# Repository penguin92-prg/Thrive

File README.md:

# Thrive 2026 Main-repo

このリポジトリは RCJ サッカー オープンリーグ に出場する、チーム Thrive のリポジトリです。

### Follow us!
様々な情報を公開していこうと考えています！ぜひのぞいてみてください！
- X (Twitter) | [@RCJ_thrive](https://x.com/RCJ_thrive)
- YouTube | [@RCJ_thrive](https://youtube.com/@rcj_thrive)
- Team Web Page | [Thrive Blog](https://note.com/rcj_thrive)

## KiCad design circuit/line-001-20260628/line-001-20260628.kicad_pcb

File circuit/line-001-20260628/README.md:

# ラインセンサ基板 001

ラインセンサ基板 ver.001のREADME

## 設計者
- @penguin92-prg
- @ryo-robot14

## ピンアサイン

## 使用上の注意

## 使用部品

|No.|Ref.|Name|QTY|Assembled By|Note|URL|
|---|---|---|---|---|---|---|
|001|D1~40|OSR5JA3Z74A|40|OWN|赤色LED|[秋月電子](https://akizukidenshi.com/catalog/g/g111577/)|
|002|R41~72,77~80|Resister 10kΩ|34|JLCPCB|LED用75Ω|[JLCPCB](https://jlcpcb.com/partdetail/21350-0805W8F750JT5E_SMTonly/C20638)|
|003|Q1~40|NJL7502L|40|OWN|フォトトランジスタ|[秋月電子](https://akizukidenshi.com/catalog/g/g102325/)|
|004|R1~32,38,40|Resister 10kΩ|34|JLCPCB|プルダウン用100kΩ|[JLCPCB](https://jlcpcb.com/partdetail/18102-0805W8F1002T5E/C17414)|
|005|U1~16,19,20|LM339DR|20|JLCPCB|コンパレータ|[JLCPCB](https://jlcpcb.com/partdetail/TexasInstruments-LM393DR/C67470)|
|006|C1~16,23,24|Capacitor 100nF|20|JLCPCB|コンパレータ用バイパスコンデンサ|[JLCPCB](https://jlcpcb.com/partdetail/YAGEO-CC0805KRX7R9BB104/C49678)|
|007|C21,22,26,27|Capacitor 10uF|4|JLCPCB|PWM平滑化用コンデンサ|[JLCPCB](https://jlcpcb.com/partdetail/439567-GRM21BR61H106KE43L/C440198)|
|008|R83,84,87,88|Resister 1kΩ|4|JLCPCB|PWM平滑化用抵抗器|[JLCPCB](https://jlcpcb.com/partdetail/18201-0805W8F1001T5E/C17513)|
|009|U17|ATMega2560-16A|1|OWN||[秋月電子](https://akizukidenshi.com/catalog/g/g116567/)|
|010|C28|Capacitor 100nF|1|JLCPCB|ATMegaARFF用コンデンサ|[JLCPCB](https://jlcpcb.com/partdetail/YAGEO-CC0805KRX7R9BB104/C49678)|
|011|SW1|TVBP06-B043C|1|OWN|ATMegaRST用白色タクトスイッチ|[秋月電子](https://akizukidenshi.com/catalog/g/g108074/)|
|012|C18|Capacitor 100nF|1|JLCPCB|ATMegaRST用コンデンサ|[JLCPCB](https://jlcpcb.com/partdetail/YAGEO-CC0805KRX7R9BB104/C49678)|
|013|R81|Resister 10kΩ|1|JLCPCB|ATMegaRST用抵抗器|[JLCPCB](https://jlcpcb.com/partdetail/18102-0805W8F1002T5E/C17414)|
|014|C20|Capacitor 100uF|1|JLCPCB|ATMega用バルクコンデンサ|[JLCPCB](https://jlcpcb.com/partdetail/15681-CL31A107MQHNNNE/C15008)|
|015|C34~38|Capacitor 100nF|5|JLCPCB|ATMega用バイパスコンデンサ|[JLCPCB](https://jlcpcb.com/partdetail/YAGEO-CC0805KRX7R9BB104/C49678)|
|016|SW2|SS12D01G4|1|OWN|5V切り替え用スライドスイッチ|[秋月電子](https://akizukidenshi.com/catalog/g/g112723/)|
|017|J3|コネクタハウジング 02x03|1|OWN|ICSP用ハウジング（配線を介すること）|[秋月電子](https://akizukidenshi.com/catalog/g/g112435/)|
|018|D41|OSG50603C1E|1|OWN|信号緑色LED|[秋月電子](https://akizukidenshi.com/catalog/g/g108275/)|
|019|D42|OSWT1608C1A|1|OWN|信号青色LED|[秋月電子](https://akizukidenshi.com/catalog/g/g103986/)|
|020|R85,86|Resister 330Ω|2|JLCPCB|LED用抵抗器|[JLCPCB](https://jlcpcb.com/partdetail/18318-0805W8F3300T5E/C17630)|
|021|U18|CH340G|1|OWN|USB-UART変換IC|[秋月電子](https://akizukidenshi.com/catalog/g/g113544/)|
|022|C31,32,33|Capacitor 100nF|3|JLCPCB|CH340G用コンデンサ|[JLCPCB](https://jlcpcb.com/partdetail/YAGEO-CC0805KRX7R9BB104/C49678)|
|023|R93|Resister 4.7kΩ|1|JLCPCB|CH340G用抵抗器|[JLCPCB](https://jlcpcb.com/partdetail/18361-0805W8F4701T5E/C17673)|
|024|Y1|Crystal 16MHz|1|OWN|クリスタル|[秋月電子](https://akizukidenshi.com/catalog/g/g108671/)|
|025|C17,19|Capacitor 22pF|2|JLCPCB|クリスタル用コンデンサ|[JLCPCB](https://jlcpcb.com/partdetail/2005-CL10C220JB8NNNC/C1653)|
|026|R82|Resister 1MΩ||JLCPCB|クリスタル用抵抗器|[JLCPCB](https://jlcpcb.com/partdetail/18202-0805W8F1004T5E/C17514)|
|027|Y2|Crystal 12MHz|1|OWN|クリスタル|[秋月電子](https://akizukidenshi.com/catalog/g/g108669/)|
|028|C29,30|Capacitor 22pF|2|JLCPCB|クリスタル用コンデンサ|[JLCPCB](https://jlcpcb.com/partdetail/2005-CL10C220JB8NNNC/C1653)|
|029|R89|Resister 1MΩ|1|JLCPCB|クリスタル用抵抗器|[JLCPCB](https://jlcpcb.com/partdetail/18202-0805W8F1004T5E/C17514)|
|030|P1|USB Type-C|1|OWN|1|[秋月電子](https://akizukidenshi.com/catalog/g/g114356/)|
|031|R90,91|Resister 5.1kΩ|2|JLCPCB|USB用抵抗器|[JLCPCB](https://jlcpcb.com/partdetail/28584-0805W8F5101T5E/C27834)|
|032|D43|CH213K|1|OWN|USB用理想ダイオード|[秋月電子](https://akizukidenshi.com/catalog/g/g129462/)|
|033|D44|OSR50603C1E|1|OWN|VBUS確認用LED|[秋月電子](https://akizukidenshi.com/catalog/g/g108274/)|
|034|R92|Resister 330Ω|1|JLCPCB|VBUS確認用抵抗器|[JLCPCB](https://jlcpcb.com/partdetail/18318-0805W8F3300T5E/C17630)|
|035|J1|XT30U-M|1|OWN|供給基板との接続|[秋月電子](https://akizukidenshi.com/catalog/g/g117951/)|
|036|J2|---|-|---|2pin配線を直接実装すること|---|

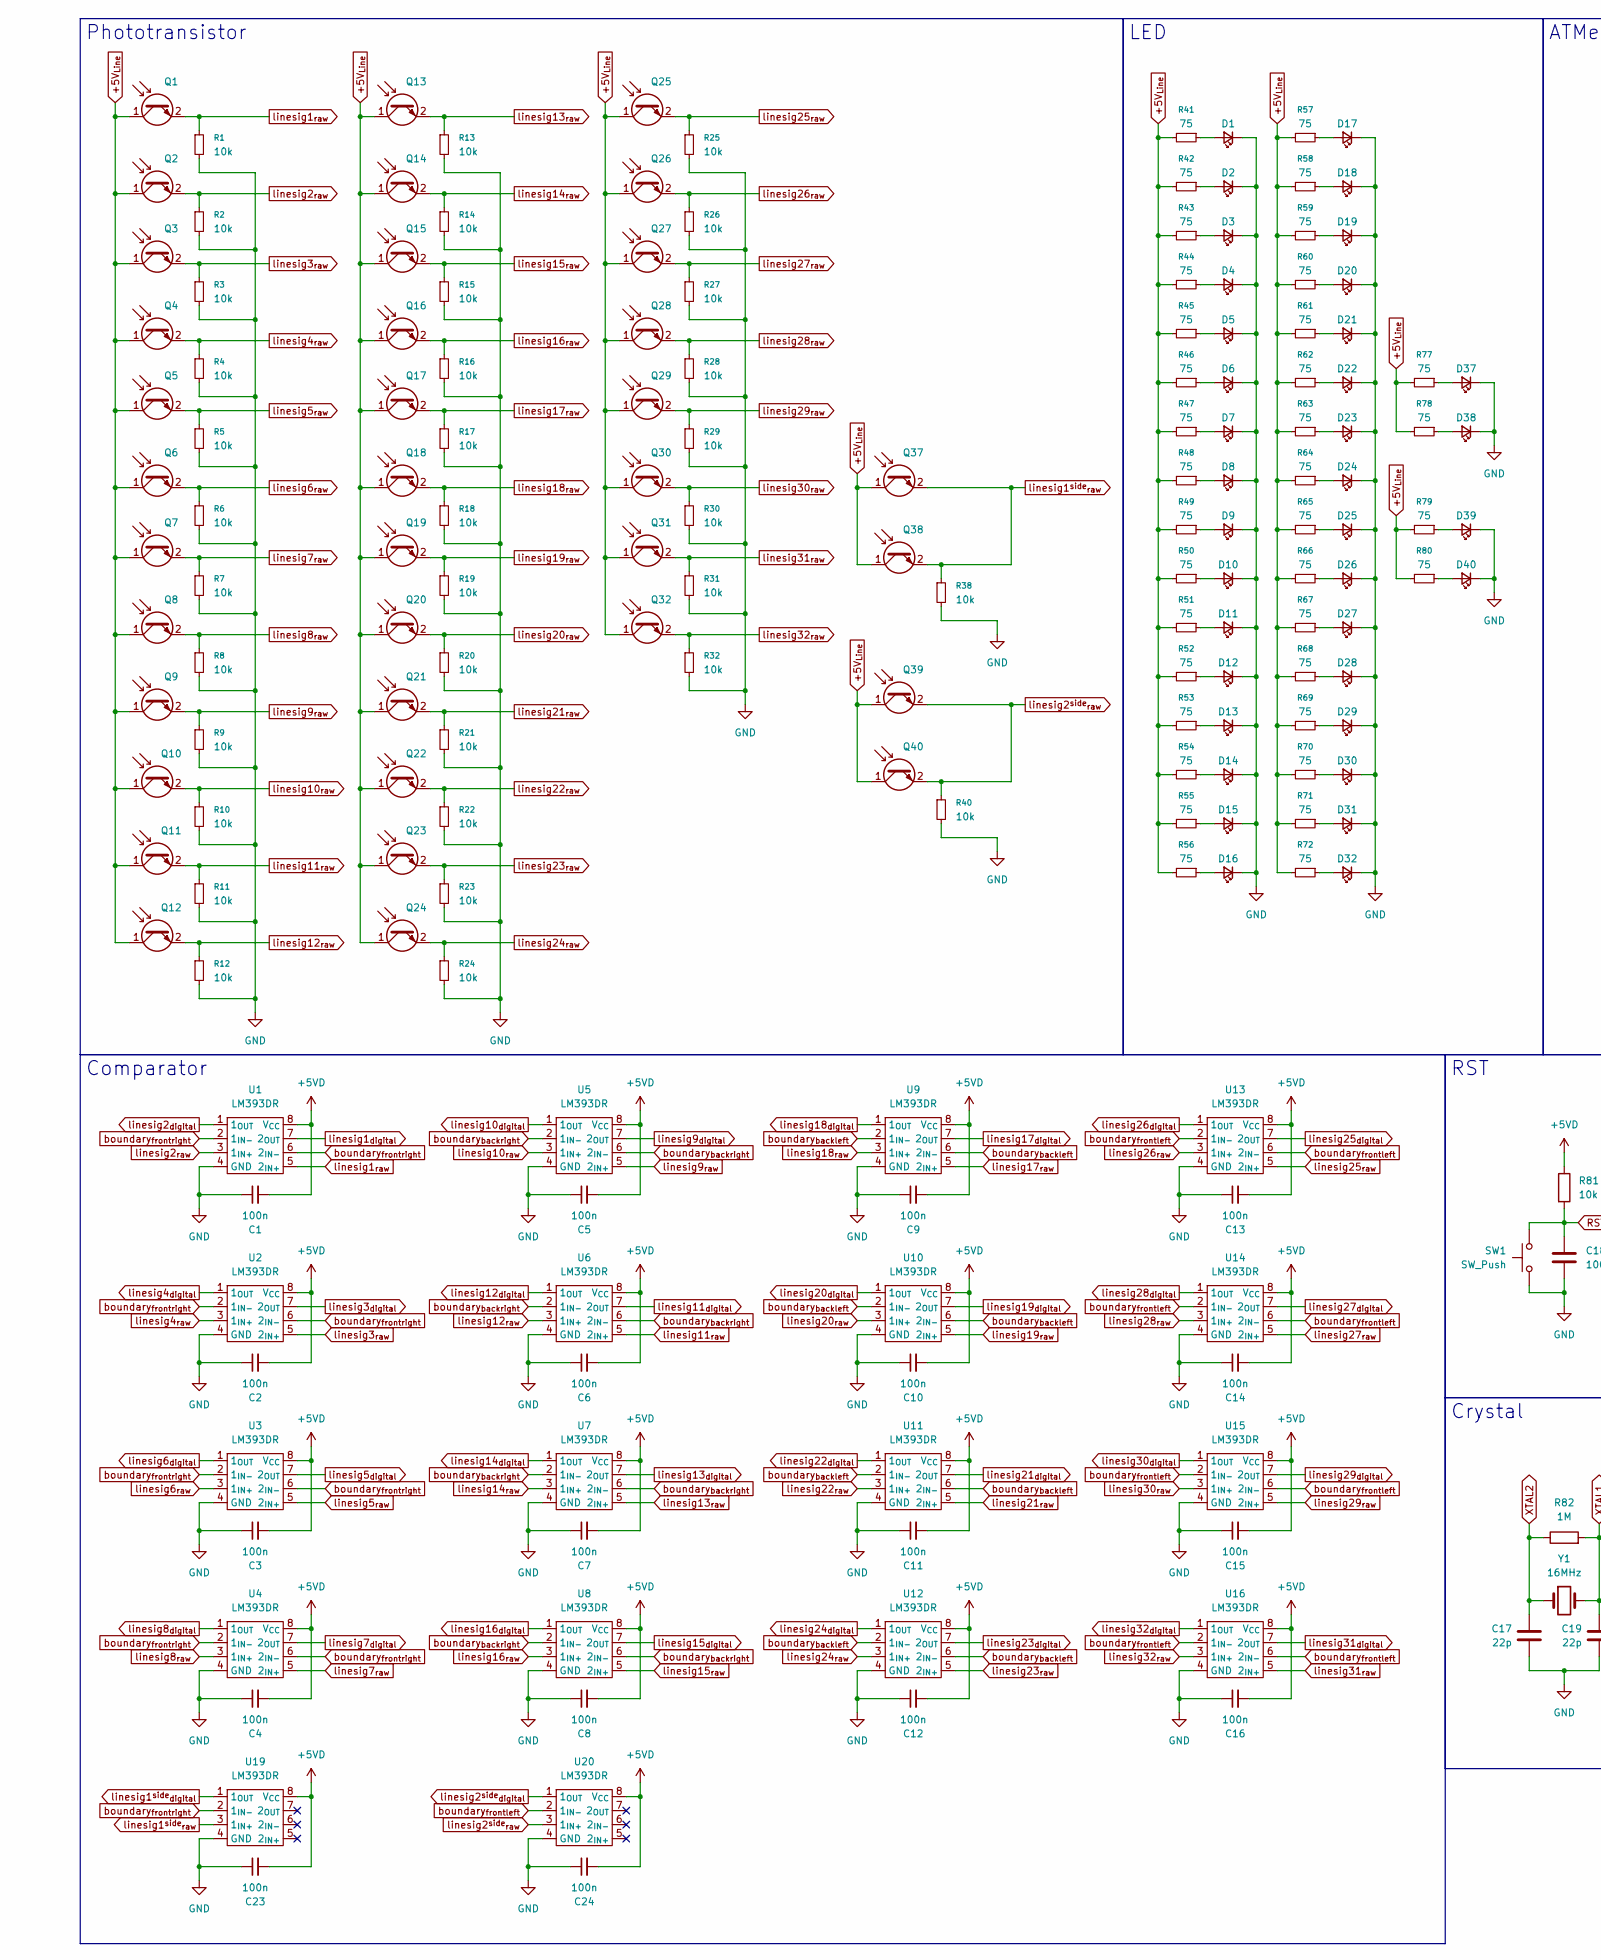
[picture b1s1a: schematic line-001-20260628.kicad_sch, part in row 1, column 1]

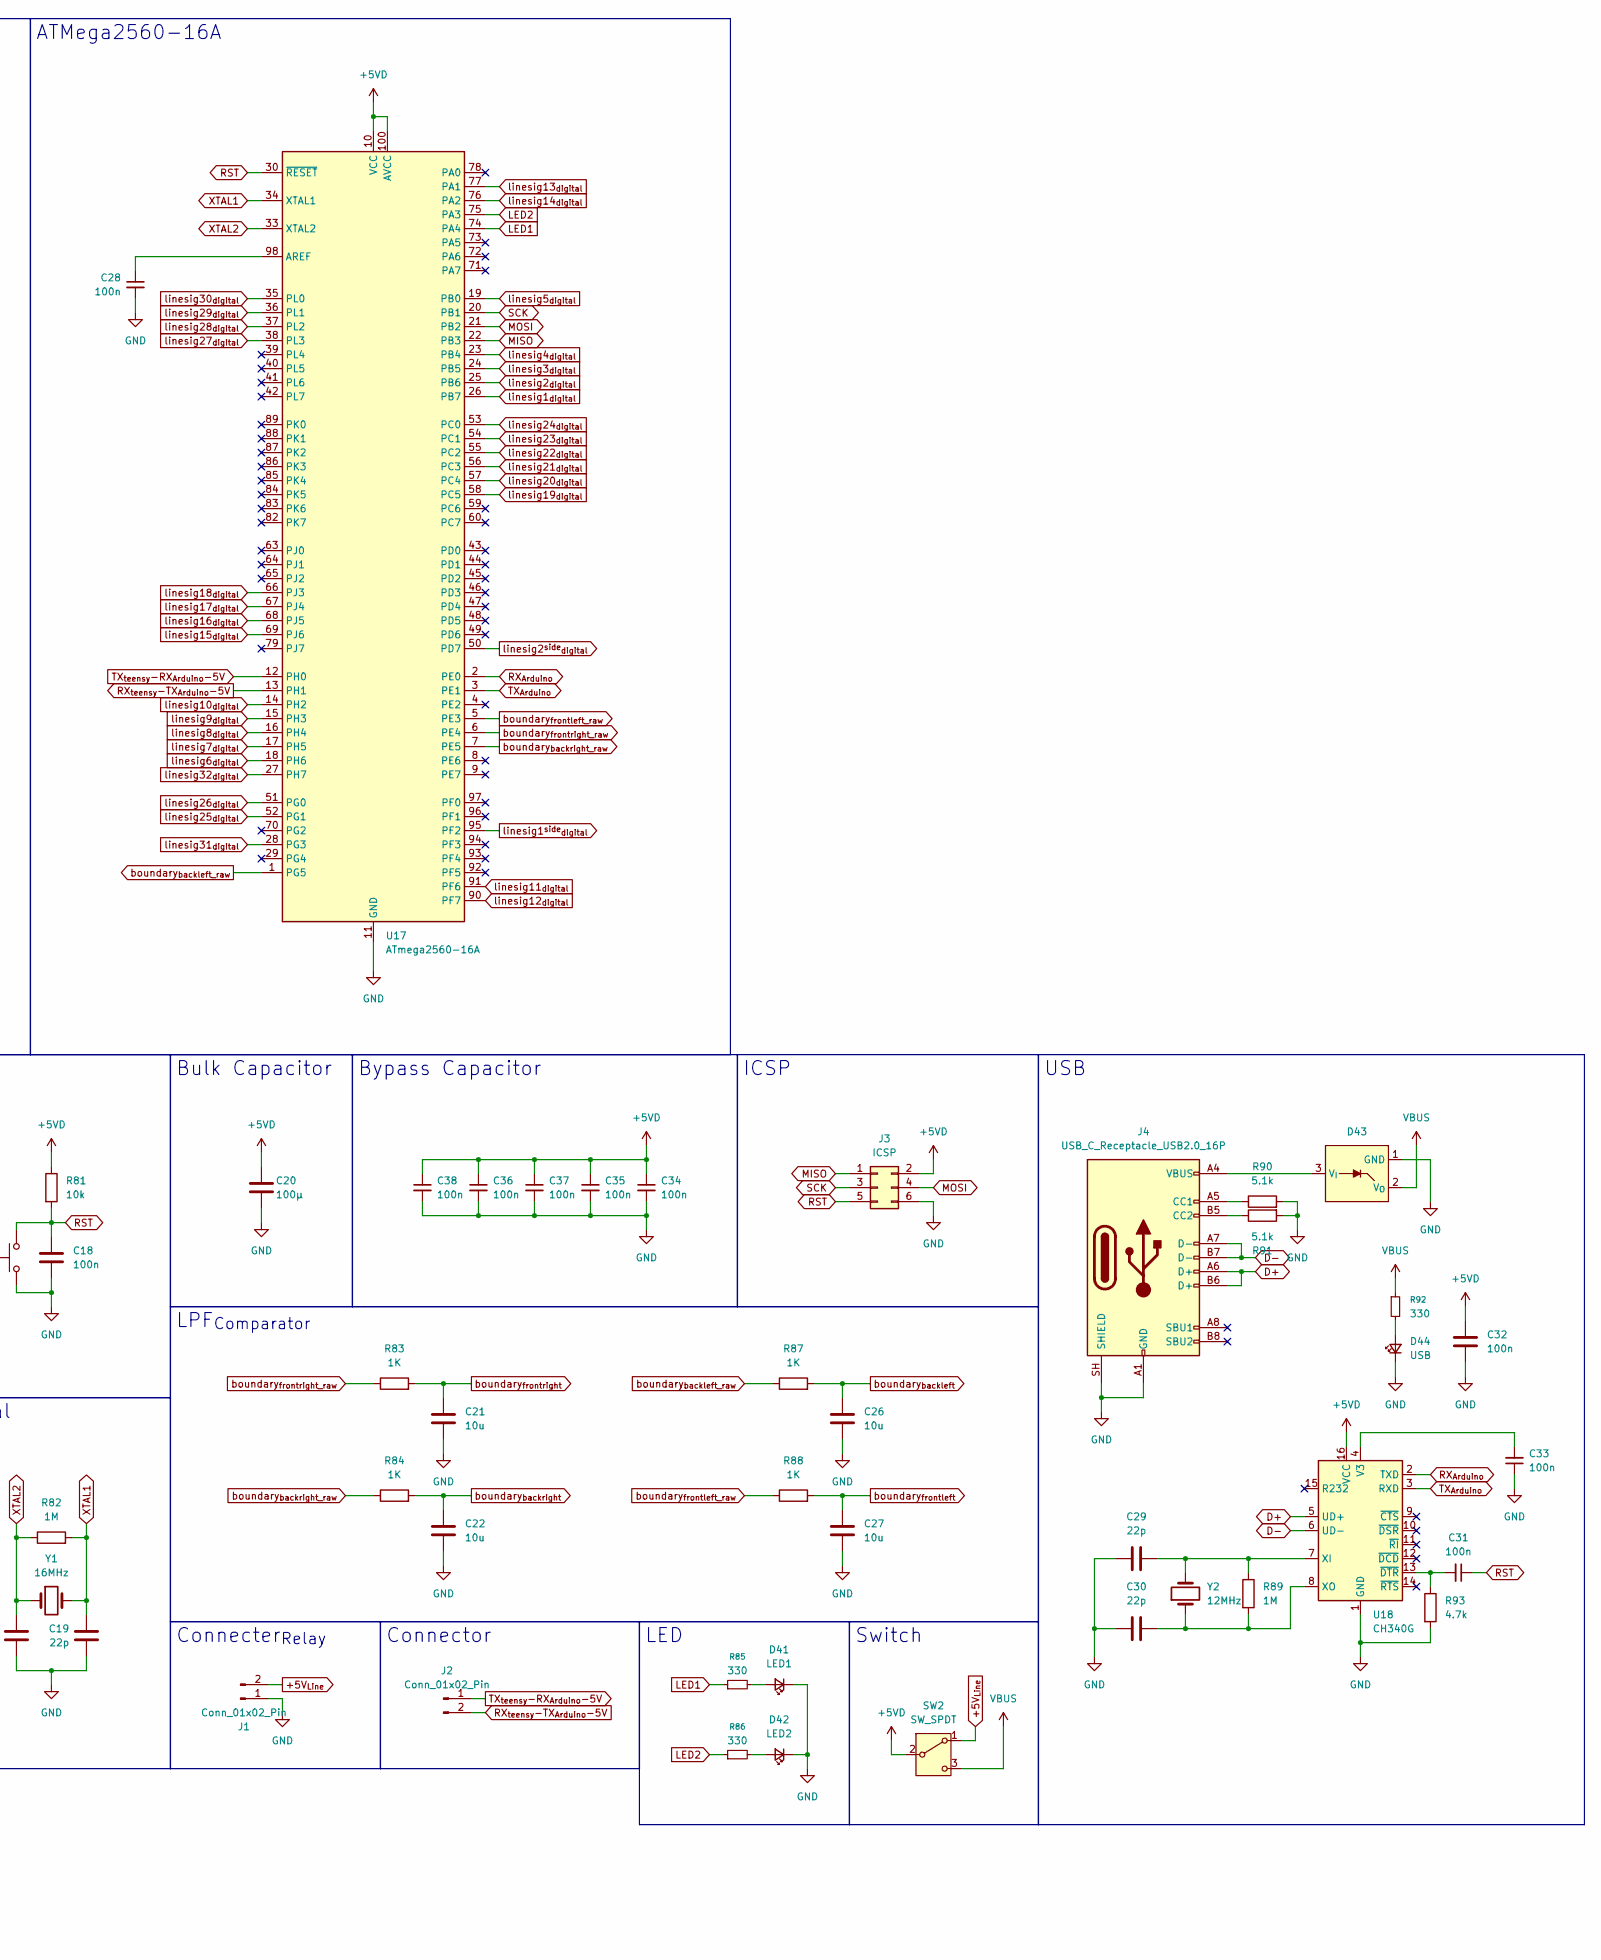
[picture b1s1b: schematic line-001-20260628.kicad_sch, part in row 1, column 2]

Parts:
C1, C2, C3, C4, C5, C6, C7, C8, C9, C10, C11, C12, C13, C14, C15, C16, C18, C23, C24, C28, C31, C32, C33, C34, C35, C36, C37, C38: 100n; C_0805_2012Metric
C17, C19, C29, C30: 22p; C_0603_1608Metric
C20: 100μ; C_1206_3216Metric
C21, C22, C26, C27: 10u; C_0805_2012Metric
D1, D2, D3, D4, D5, D6, D7, D8, D9, D10, D11, D12, D13, D14, D15, D16, D17, D18, D19, D20, D21, D22, D23, D24, D25, D26, D27, D28, D29, D30, D31, D32, D37, D38, D39, D40: LED_Small; LED_D3.0mm
D41: LED1; LED_0603_1608Metric
D42: LED2; LED_0603_1608Metric
D43: TSOT-23
D44: USB; LED_0603_1608Metric
J1: Conn_01x02_Pin; AMASS_XT30U-M_1x02_P5.0mm_Vertical
J2: Conn_01x02_Pin; Conn_01x02_Wire_Only
J3: ICSP; PinHeader_2x03_P2.54mm_Vertical
J4: USB_C_Receptacle_USB2.0_16P; USB_C_Receptacle_HCTL_HC-TYPE-C-16P-01A
Q1, Q2, Q3, Q4, Q5, Q6, Q7, Q8, Q9, Q10, Q11, Q12, Q13, Q14, Q15, Q16, Q17, Q18, Q19, Q20, Q21, Q22, Q23, Q24, Q25, Q26, Q27, Q28, Q29, Q30, Q31, Q32, Q37, Q38, Q39, Q40: Q_Photo_NPN_CE; NJL7502L
R1, R2, R3, R4, R5, R6, R7, R8, R9, R10, R11, R12, R13, R14, R15, R16, R17, R18, R19, R20, R21, R22, R23, R24, R25, R26, R27, R28, R29, R30, R31, R32, R38, R40, R81: 10k; R_0805_2012Metric
R41, R42, R43, R44, R45, R46, R47, R48, R49, R50, R51, R52, R53, R54, R55, R56, R57, R58, R59, R60, R61, R62, R63, R64, R65, R66, R67, R68, R69, R70, R71, R72, R77, R78, R79, R80: 75; R_0805_2012Metric
R82, R89: 1M; R_0805_2012Metric
R83, R84, R87, R88: 1K; R_0805_2012Metric
R85, R86, R92: 330; R_0805_2012Metric
R90, R91: 5.1k; R_0805_2012Metric
R93: 4.7k; R_0805_2012Metric
SW1: SW_Push; TVBP06-B043C
SW2: SW_SPDT; SS12D01G4
U1, U2, U3, U4, U5, U6, U7, U8, U9, U10, U11, U12, U13, U14, U15, U16, U19, U20: LM393DR; SOIC-8_3.9x4.9mm_P1.27mm
U17: ATmega2560-16A; TQFP-100_14x14mm_P0.5mm
U18: CH340G; SOIC-16_3.9x9.9mm_P1.27mm
Y1: 16MHz; Crystal_SMD_SeikoEpson_FA238-4Pin_3.2x2.5mm
Y2: 12MHz; Crystal_SMD_SeikoEpson_FA238V-4Pin_3.2x2.5mm

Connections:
+5VD: C1.2, C2.2, C3.2, C4.2, C5.2, C6.2, C7.2, C8.2, C9.2, C10.2, C11.2, C12.2, C13.2, C14.2, C15.2, C16.2, C20.1, C23.2, C24.2, C32.2, C34.1, C35.1, C36.1, C37.1, C38.1, J3.2, R81.1, SW2.2 (B), U1.8 (V_{CC}), U2.8 (V_{CC}), U3.8 (V_{CC}), U4.8 (V_{CC}), U5.8 (V_{CC}), U6.8 (V_{CC}), U7.8 (V_{CC}), U8.8 (V_{CC}), U9.8 (V_{CC}), U10.8 (V_{CC}), U11.8 (V_{CC}), U12.8 (V_{CC}), U13.8 (V_{CC}), U14.8 (V_{CC}), U15.8 (V_{CC}), U16.8 (V_{CC}), U17.10 (VCC), U17.31 (VCC), U17.61 (VCC), U17.80 (VCC), U17.100 (AVCC), U18.16 (VCC), U19.8 (V_{CC}), U20.8 (V_{CC})
+5V_{Line}: J1.2, Q1.1 (C), Q2.1 (C), Q3.1 (C), Q4.1 (C), Q5.1 (C), Q6.1 (C), Q7.1 (C), Q8.1 (C), Q9.1 (C), Q10.1 (C), Q11.1 (C), Q12.1 (C), Q13.1 (C), Q14.1 (C), Q15.1 (C), Q16.1 (C), Q17.1 (C), Q18.1 (C), Q19.1 (C), Q20.1 (C), Q21.1 (C), Q22.1 (C), Q23.1 (C), Q24.1 (C), Q25.1 (C), Q26.1 (C), Q27.1 (C), Q28.1 (C), Q29.1 (C), Q30.1 (C), Q31.1 (C), Q32.1 (C), Q37.1 (C), Q38.1 (C), Q39.1 (C), Q40.1 (C), R41.2, R42.2, R43.2, R44.2, R45.2, R46.2, R47.2, R48.2, R49.2, R50.2, R51.2, R52.2, R53.2, R54.2, R55.2, R56.2, R57.2, R58.2, R59.2, R60.2, R61.2, R62.2, R63.2, R64.2, R65.2, R66.2, R67.2, R68.2, R69.2, R70.2, R71.2, R72.2, R77.2, R78.2, R79.2, R80.2, SW2.1 (A)
D+: J4.A6 (D+), J4.B6 (D+), U18.5 (UD+)
D-: J4.A7 (D-), J4.B7 (D-), U18.6 (UD-)
GND: C1.1, C2.1, C3.1, C4.1, C5.1, C6.1, C7.1, C8.1, C9.1, C10.1, C11.1, C12.1, C13.1, C14.1, C15.1, C16.1, C17.2, C18.2, C19.2, C20.2, C21.2, C22.2, C23.1, C24.1, C26.2, C27.2, C28.2, C29.1, C30.1, C32.1, C33.1, C34.2, C35.2, C36.2, C37.2, C38.2, D1.1 (K), D2.1 (K), D3.1 (K), D4.1 (K), D5.1 (K), D6.1 (K), D7.1 (K), D8.1 (K), D9.1 (K), D10.1 (K), D11.1 (K), D12.1 (K), D13.1 (K), D14.1 (K), D15.1 (K), D16.1 (K), D17.1 (K), D18.1 (K), D19.1 (K), D20.1 (K), D21.1 (K), D22.1 (K), D23.1 (K), D24.1 (K), D25.1 (K), D26.1 (K), D27.1 (K), D28.1 (K), D29.1 (K), D30.1 (K), D31.1 (K), D32.1 (K), D37.1 (K), D38.1 (K), D39.1 (K), D40.1 (K), D41.1 (K), D42.1 (K), D43.1 (GND), D44.1 (K), J1.1, J3.6, J4.A1 (GND), J4.A12 (GND), J4.B1 (GND), J4.B12 (GND), J4.SH (SHIELD), R1.2, R2.2, R3.2, R4.2, R5.2, R6.2, R7.2, R8.2, R9.2, R10.2, R11.2, R12.2, R13.2, R14.2, R15.2, R16.2, R17.2, R18.2, R19.2, R20.2, R21.2, R22.2, R23.2, R24.2, R25.2, R26.2, R27.2, R28.2, R29.2, R30.2, R31.2, R32.2, R38.2, R40.2, R90.2, R91.2, R93.2, SW1.1, U1.4 (GND), U2.4 (GND), U3.4 (GND), U4.4 (GND), U5.4 (GND), U6.4 (GND), U7.4 (GND), U8.4 (GND), U9.4 (GND), U10.4 (GND), U11.4 (GND), U12.4 (GND), U13.4 (GND), U14.4 (GND), U15.4 (GND), U16.4 (GND), U17.11 (GND), U17.32 (GND), U17.62 (GND), U17.81 (GND), U17.99 (GND), U18.1 (GND), U19.4 (GND), U20.4 (GND)
LED1: R85.1, U17.74 (PA4)
LED2: R86.1, U17.75 (PA3)
MISO: J3.1, U17.22 (PB3)
MOSI: J3.4, U17.21 (PB2)
unnamed: D1.2 (A), R41.1
unnamed: D2.2 (A), R42.1
unnamed: D3.2 (A), R43.1
unnamed: D4.2 (A), R44.1
unnamed: D5.2 (A), R45.1
unnamed: D6.2 (A), R46.1
unnamed: D7.2 (A), R47.1
unnamed: D8.2 (A), R48.1
unnamed: D9.2 (A), R49.1
unnamed: D10.2 (A), R50.1
unnamed: D11.2 (A), R51.1
unnamed: D12.2 (A), R52.1
unnamed: D13.2 (A), R53.1
unnamed: D14.2 (A), R54.1
unnamed: D15.2 (A), R55.1
unnamed: D16.2 (A), R56.1
unnamed: D17.2 (A), R57.1
unnamed: D18.2 (A), R58.1
unnamed: D19.2 (A), R59.1
unnamed: D20.2 (A), R60.1
unnamed: D21.2 (A), R61.1
unnamed: D22.2 (A), R62.1
unnamed: D23.2 (A), R63.1
unnamed: D24.2 (A), R64.1
unnamed: D25.2 (A), R65.1
unnamed: D26.2 (A), R66.1
unnamed: D27.2 (A), R67.1
unnamed: D28.2 (A), R68.1
unnamed: D29.2 (A), R69.1
unnamed: D30.2 (A), R70.1
unnamed: D31.2 (A), R71.1
unnamed: D32.2 (A), R72.1
unnamed: D37.2 (A), R77.1
unnamed: D38.2 (A), R78.1
unnamed: D39.2 (A), R79.1
unnamed: D40.2 (A), R80.1
unnamed: D41.2 (A), R85.2
unnamed: D42.2 (A), R86.2
unnamed: D43.3 (V_{I}), J4.A4 (VBUS), J4.A9 (VBUS), J4.B4 (VBUS), J4.B9 (VBUS)
unnamed: D44.2 (A), R92.2
unnamed: J4.A5 (CC1), R90.1
unnamed: J4.B5 (CC2), R91.1
unnamed: C28.1, U17.98 (AREF)
unnamed: C33.2, U18.4 (V3)
unnamed: C29.2, R89.1, U18.7 (XI), Y2.3
unnamed: C30.2, R89.2, U18.8 (XO), Y2.1
unnamed: C31.2, R93.1, U18.13 (~DTR)
RST: C18.1, C31.1, J3.5, R81.2, SW1.2, U17.30 (~RESET)
RX_{Arduino}: U17.2 (PE0), U18.2 (TXD)
RX_{teensy}-TX_{Arduino}-5V: J2.2, U17.13 (PH1)
SCK: J3.3, U17.20 (PB1)
TX_{Arduino}: U17.3 (PE1), U18.3 (RXD)
TX_{teensy}-RX_{Arduino}-5V: J2.1, U17.12 (PH0)
VBUS: D43.2 (V_{O}), R92.1, SW2.3 (C)
XTAL1: C19.1, R82.2, U17.34 (XTAL1), Y1.3
XTAL2: C17.1, R82.1, U17.33 (XTAL2), Y1.1
boundary_{backleft_raw}: R87.1, U17.1 (PG5)
boundary_{backleft}: C26.1, R87.2, U9.2 (1_{IN-}), U9.6 (2_{IN-}), U10.2 (1_{IN-}), U10.6 (2_{IN-}), U11.2 (1_{IN-}), U11.6 (2_{IN-}), U12.2 (1_{IN-}), U12.6 (2_{IN-})
boundary_{backright_raw}: R84.1, U17.7 (PE5)
boundary_{backright}: C22.1, R84.2, U5.2 (1_{IN-}), U5.6 (2_{IN-}), U6.2 (1_{IN-}), U6.6 (2_{IN-}), U7.2 (1_{IN-}), U7.6 (2_{IN-}), U8.2 (1_{IN-}), U8.6 (2_{IN-})
boundary_{frontleft_raw}: R88.1, U17.5 (PE3)
boundary_{frontleft}: C27.1, R88.2, U13.2 (1_{IN-}), U13.6 (2_{IN-}), U14.2 (1_{IN-}), U14.6 (2_{IN-}), U15.2 (1_{IN-}), U15.6 (2_{IN-}), U16.2 (1_{IN-}), U16.6 (2_{IN-}), U20.2 (1_{IN-})
boundary_{frontright_raw}: R83.1, U17.6 (PE4)
boundary_{frontright}: C21.1, R83.2, U1.2 (1_{IN-}), U1.6 (2_{IN-}), U2.2 (1_{IN-}), U2.6 (2_{IN-}), U3.2 (1_{IN-}), U3.6 (2_{IN-}), U4.2 (1_{IN-}), U4.6 (2_{IN-}), U19.2 (1_{IN-})
linesig1^{side}_{digital}: U17.95 (PF2), U19.1 (1_{OUT})
linesig1^{side}_{raw}: Q37.2 (E), Q38.2 (E), R38.1, U19.3 (1_{IN+})
linesig1_{digital}: U1.7 (2_{OUT}), U17.26 (PB7)
linesig1_{raw}: Q1.2 (E), R1.1, U1.5 (2_{IN+})
linesig2^{side}_{digital}: U17.50 (PD7), U20.1 (1_{OUT})
linesig2^{side}_{raw}: Q39.2 (E), Q40.2 (E), R40.1, U20.3 (1_{IN+})
linesig2_{digital}: U1.1 (1_{OUT}), U17.25 (PB6)
linesig2_{raw}: Q2.2 (E), R2.1, U1.3 (1_{IN+})
linesig3_{digital}: U2.7 (2_{OUT}), U17.24 (PB5)
linesig3_{raw}: Q3.2 (E), R3.1, U2.5 (2_{IN+})
linesig4_{digital}: U2.1 (1_{OUT}), U17.23 (PB4)
linesig4_{raw}: Q4.2 (E), R4.1, U2.3 (1_{IN+})
linesig5_{digital}: U3.7 (2_{OUT}), U17.19 (PB0)
linesig5_{raw}: Q5.2 (E), R5.1, U3.5 (2_{IN+})
linesig6_{digital}: U3.1 (1_{OUT}), U17.18 (PH6)
linesig6_{raw}: Q6.2 (E), R6.1, U3.3 (1_{IN+})
linesig7_{digital}: U4.7 (2_{OUT}), U17.17 (PH5)
linesig7_{raw}: Q7.2 (E), R7.1, U4.5 (2_{IN+})
linesig8_{digital}: U4.1 (1_{OUT}), U17.16 (PH4)
linesig8_{raw}: Q8.2 (E), R8.1, U4.3 (1_{IN+})
linesig9_{digital}: U5.7 (2_{OUT}), U17.15 (PH3)
linesig9_{raw}: Q9.2 (E), R9.1, U5.5 (2_{IN+})
linesig10_{digital}: U5.1 (1_{OUT}), U17.14 (PH2)
linesig10_{raw}: Q10.2 (E), R10.1, U5.3 (1_{IN+})
linesig11_{digital}: U6.7 (2_{OUT}), U17.91 (PF6)
linesig11_{raw}: Q11.2 (E), R11.1, U6.5 (2_{IN+})
linesig12_{digital}: U6.1 (1_{OUT}), U17.90 (PF7)
linesig12_{raw}: Q12.2 (E), R12.1, U6.3 (1_{IN+})
linesig13_{digital}: U7.7 (2_{OUT}), U17.77 (PA1)
linesig13_{raw}: Q13.2 (E), R13.1, U7.5 (2_{IN+})
linesig14_{digital}: U7.1 (1_{OUT}), U17.76 (PA2)
linesig14_{raw}: Q14.2 (E), R14.1, U7.3 (1_{IN+})
linesig15_{digital}: U8.7 (2_{OUT}), U17.69 (PJ6)
linesig15_{raw}: Q15.2 (E), R15.1, U8.5 (2_{IN+})
linesig16_{digital}: U8.1 (1_{OUT}), U17.68 (PJ5)
linesig16_{raw}: Q16.2 (E), R16.1, U8.3 (1_{IN+})
linesig17_{digital}: U9.7 (2_{OUT}), U17.67 (PJ4)
linesig17_{raw}: Q17.2 (E), R17.1, U9.5 (2_{IN+})
linesig18_{digital}: U9.1 (1_{OUT}), U17.66 (PJ3)
linesig18_{raw}: Q18.2 (E), R18.1, U9.3 (1_{IN+})
linesig19_{digital}: U10.7 (2_{OUT}), U17.58 (PC5)
linesig19_{raw}: Q19.2 (E), R19.1, U10.5 (2_{IN+})
linesig20_{digital}: U10.1 (1_{OUT}), U17.57 (PC4)
linesig20_{raw}: Q20.2 (E), R20.1, U10.3 (1_{IN+})
linesig21_{digital}: U11.7 (2_{OUT}), U17.56 (PC3)
linesig21_{raw}: Q21.2 (E), R21.1, U11.5 (2_{IN+})
linesig22_{digital}: U11.1 (1_{OUT}), U17.55 (PC2)
linesig22_{raw}: Q22.2 (E), R22.1, U11.3 (1_{IN+})
linesig23_{digital}: U12.7 (2_{OUT}), U17.54 (PC1)
linesig23_{raw}: Q23.2 (E), R23.1, U12.5 (2_{IN+})
linesig24_{digital}: U12.1 (1_{OUT}), U17.53 (PC0)
linesig24_{raw}: Q24.2 (E), R24.1, U12.3 (1_{IN+})
linesig25_{digital}: U13.7 (2_{OUT}), U17.52 (PG1)
linesig25_{raw}: Q25.2 (E), R25.1, U13.5 (2_{IN+})
linesig26_{digital}: U13.1 (1_{OUT}), U17.51 (PG0)
linesig26_{raw}: Q26.2 (E), R26.1, U13.3 (1_{IN+})
linesig27_{digital}: U14.7 (2_{OUT}), U17.38 (PL3)
linesig27_{raw}: Q27.2 (E), R27.1, U14.5 (2_{IN+})
linesig28_{digital}: U14.1 (1_{OUT}), U17.37 (PL2)
linesig28_{raw}: Q28.2 (E), R28.1, U14.3 (1_{IN+})
linesig29_{digital}: U15.7 (2_{OUT}), U17.36 (PL1)
linesig29_{raw}: Q29.2 (E), R29.1, U15.5 (2_{IN+})
linesig30_{digital}: U15.1 (1_{OUT}), U17.35 (PL0)
linesig30_{raw}: Q30.2 (E), R30.1, U15.3 (1_{IN+})
linesig31_{digital}: U16.7 (2_{OUT}), U17.28 (PG3)
linesig31_{raw}: Q31.2 (E), R31.1, U16.5 (2_{IN+})
linesig32_{digital}: U16.1 (1_{OUT}), U17.27 (PH7)
linesig32_{raw}: Q32.2 (E), R32.1, U16.3 (1_{IN+})

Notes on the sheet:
Phototransistor
Bypass Capacitor
LED
Switch
Bulk Capacitor
Connecter_{Relay}
ATMega2560-16A
LPF_{Comparator}
Comparator
RST
ICSP
Connector
USB
Crystal

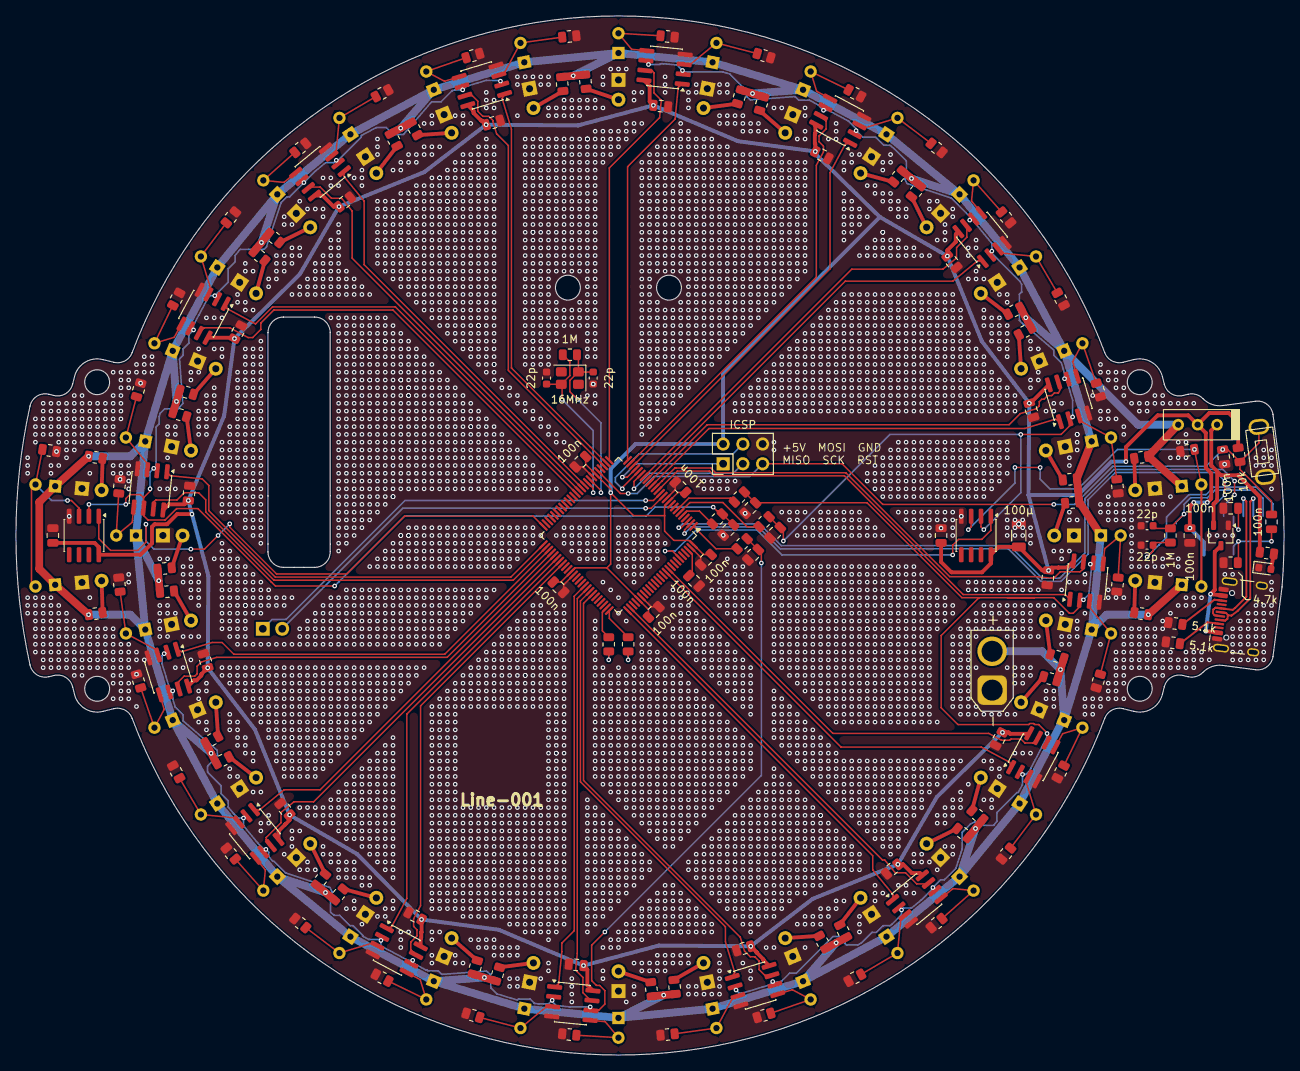
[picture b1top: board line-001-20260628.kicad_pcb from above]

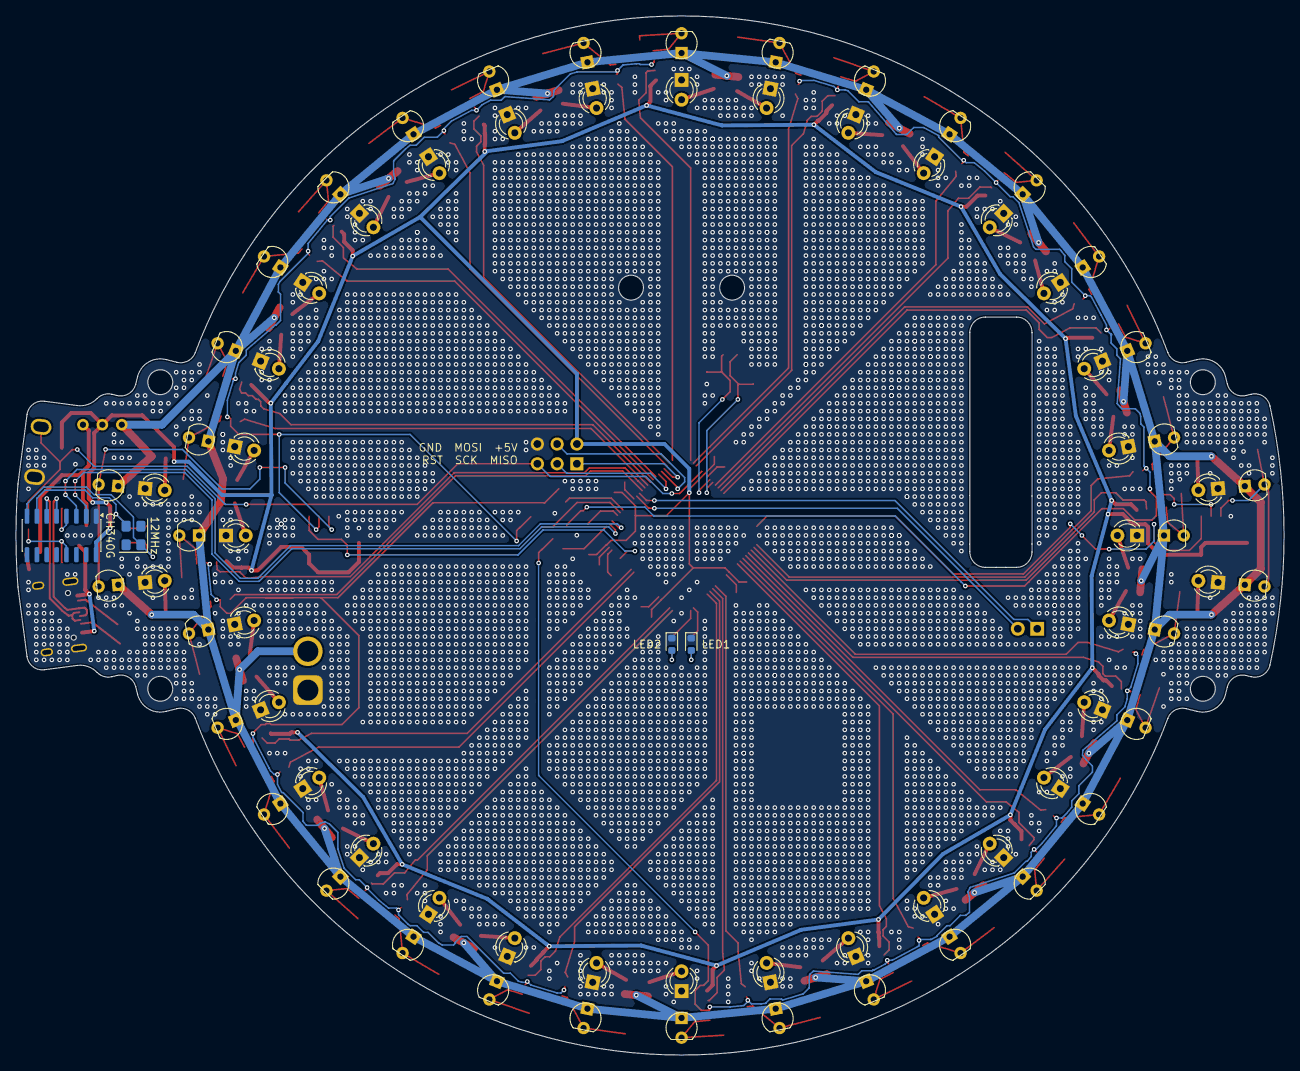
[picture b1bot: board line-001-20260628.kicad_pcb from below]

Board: 2 copper layers, 163.1 x 133.7 mm, 224 parts (76 on the bottom side), 141 nets.

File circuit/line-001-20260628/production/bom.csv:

Designator,Footprint,Quantity,Value,LCSC Part #
"C1, C10, C11, C12, C13, C14, C15, C16, C18, C2, C28, C3, C31, C32, C33, C34, C35, C36, C37, C38, C4, C5, C6, C7, C8, C9",0805,26,100n,
"C17, C19, C29, C30",0603,4,22p,
C20,1206,1,100μ,
"C21, C22, C26, C27",0805,4,C,
"D1, D10, D11, D12, D13, D14, D15, D16, D17, D18, D19, D2, D20, D21, D22, D23, D24, D25, D26, D27, D28, D29, D3, D30, D31, D32, D37, D38, D39, D4, D40, D5, D6, D7, D8, D9",LED_D3.0mm,36,LED_Small,
D41,0603,1,LED1,
D42,0603,1,LED2,
D43,TSOT-23,1,~,
D44,0603,1,USB,
J1,AMASS_XT30U-M_1x02_P5.0mm_Vertical,1,Conn_01x02_Pin,
J2,Conn_01x02_Wire_Only,1,Conn_01x02_Pin,
J3,PinHeader_2x03_P2.54mm_Vertical,1,ICSP,
J4,USB_C_Receptacle_HCTL_HC-TYPE-C-16P-01A,1,USB_C_Receptacle_USB2.0_16P,
"Q1, Q10, Q11, Q12, Q13, Q14, Q15, Q16, Q17, Q18, Q19, Q2, Q20, Q21, Q22, Q23, Q24, Q25, Q26, Q27, Q28, Q29, Q3, Q30, Q31, Q32, Q37, Q38, Q39, Q4, Q40, Q5, Q6, Q7, Q8, Q9",NJL7502L,36,Q_Photo_NPN_CE,
"R1, R10, R11, R12, R13, R14, R15, R16, R17, R18, R19, R2, R20, R21, R22, R23, R24, R25, R26, R27, R28, R29, R3, R30, R31, R32, R38, R4, R40, R5, R6, R7, R8, R81, R9",0805,35,10k,
"R41, R42, R43, R44, R45, R46, R47, R48, R49, R50, R51, R52, R53, R54, R55, R56, R57, R58, R59, R60, R61, R62, R63, R64, R65, R66, R67, R68, R69, R70, R71, R72, R77, R78, R79, R80",0805,36,75,
"R82, R89",0805,2,1M,
"R83, R84, R87, R88",0805,4,R,
"R85, R86, R92",0805,3,330,
"R90, R91",0805,2,5.1k,
R93,0805,1,4.7k,
SW1,TVBP06-B043C,1,SW_Push,
SW2,SS12D01G4,1,SW_SPDT,
"U1, U10, U11, U12, U13, U14, U15, U16, U2, U3, U4, U5, U6, U7, U8, U9",SOIC-8_3.9x4.9mm_P1.27mm,16,LM393DR,
U17,TQFP-100_14x14mm_P0.5mm,1,ATmega2560-16A,
U18,SOIC-16_3.9x9.9mm_P1.27mm,1,CH340G,
Y1,Crystal_SMD_SeikoEpson_FA238-4Pin_3.2x2.5mm,1,16MHz,
Y2,Crystal_SMD_SeikoEpson_FA238V-4Pin_3.2x2.5mm,1,12MHz,

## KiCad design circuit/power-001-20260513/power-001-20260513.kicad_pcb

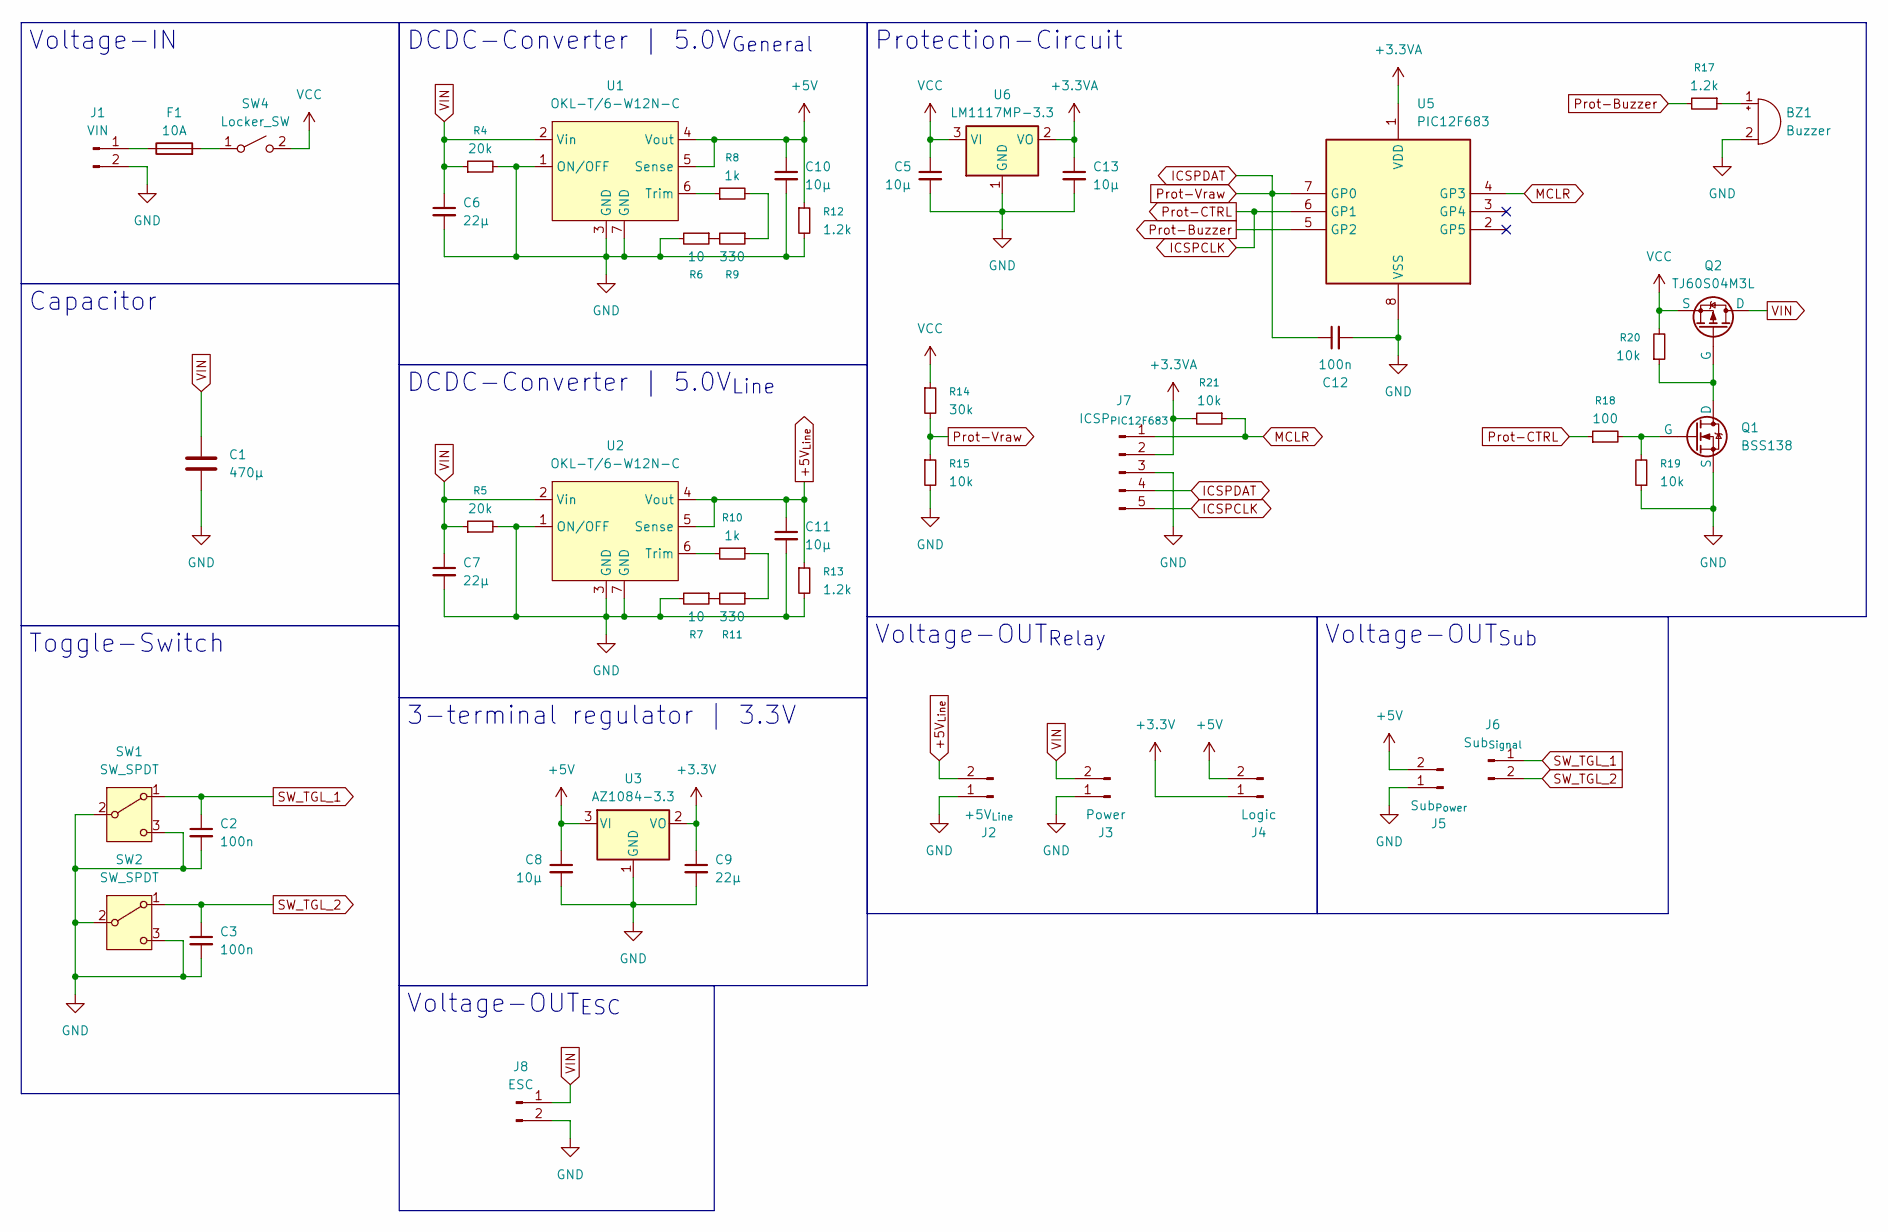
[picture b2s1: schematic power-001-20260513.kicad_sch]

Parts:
BZ1: Buzzer; PKM13EPYH4000-A0
C1: 470μ; CP_Radial_D8.0mm_P3.50mm
C2, C3, C12: 100n; C_0805_2012Metric
C5, C8, C10, C11, C13: 10μ; C_0805_2012Metric
C6, C7, C9: 22μ; C_0805_2012Metric
F1: 10A; MF61NR_FUC-04
J1: VIN; Conn_01x02_Wire_Only
J2: +5V_{Line}; AMASS_XT30PW-F_1x02_P2.50mm_Horizontal
J3: Power; AMASS_XT30PW-F_1x02_P2.50mm_Horizontal
J4: Logic; AMASS_XT30PW-F_1x02_P2.50mm_Horizontal
J5: Sub_{Power}; AMASS_XT30PW-F_1x02_P2.50mm_Horizontal
J6: Sub_{Signal}; PinHeader_1x02_P2.54mm_Horizontal
J7: ICSP_{PIC12F683}; PinHeader_1x05_P1.00mm_Vertical
J8: ESC; Conn_01x02_Wire_Only_SMD
Q1: BSS138; TSOT-23
Q2: TJ60S04M3L; TO-252-2
R4, R5: 20k; R_0805_2012Metric
R6, R7: 10; R_0805_2012Metric
R8, R10: 1k; R_0805_2012Metric
R9, R11: 330; R_0805_2012Metric
R12, R13, R17: 1.2k; R_0805_2012Metric
R14: 30k; R_0805_2012Metric
R15, R19, R20, R21: 10k; R_0805_2012Metric
R18: 100; R_0805_2012Metric
SW1, SW2: SW_SPDT; 2MS1-T1-B4-M2-Q-E
SW4: Locker_SW; DS-850K-S-ON-K
U1, U2: OKL-T/6-W12N-C; OKL-T6-W12N-C
U3: AZ1084-3.3; TO-252-2
U5: PIC12F683; SOIC-8_3.9x4.9mm_P1.27mm
U6: LM1117MP-3.3; SOT-223-3_TabPin2

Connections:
+3.3V: C9.1, J4.1, U3.2 (VO)
+3.3VA: C13.1, J7.2, R21.2, U5.1 (VDD), U6.2 (VO)
+5V: C8.1, C10.1, J4.2, J5.2, R12.1, U1.4 (Vout), U1.5 (Sense), U3.3 (VI)
+5V_{Line}: C11.1, J2.2, R13.1, U2.4 (Vout), U2.5 (Sense)
GND: BZ1.2 (-), C1.2, C2.2, C3.2, C5.2, C6.2, C7.2, C8.2, C9.2, C10.2, C11.2, C12.2, C13.2, J1.2, J2.1, J3.1, J5.1, J7.3, J8.2, Q1.3 (S), R4.2, R5.2, R6.2, R7.2, R12.2, R13.2, R15.2, R19.1, SW1.2 (B), SW1.3 (C), SW2.2 (B), SW2.3 (C), U1.1 (ON/OFF), U1.3 (GND), U1.7 (GND), U2.1 (ON/OFF), U2.3 (GND), U2.7 (GND), U3.1 (GND), U5.8 (VSS), U6.1 (GND)
ICSPCLK: J7.5, R18.1, U5.6 (GP1)
ICSPDAT: C12.1, J7.4, R14.2, R15.1, U5.7 (GP0)
MCLR: J7.1, R21.1, U5.4 (GP3)
unnamed: BZ1.1 (+), R17.1
unnamed: F1.1, J1.1
unnamed: Q1.1 (D), Q2.1 (G), R20.1
unnamed: Q1.2 (G), R18.2, R19.2
unnamed: R6.1, R9.2
unnamed: R8.2, R9.1
unnamed: R10.1, R11.1
unnamed: R7.1, R11.2
unnamed: F1.2, SW4.1 (A)
unnamed: R8.1, U1.6 (Trim)
unnamed: R10.2, U2.6 (Trim)
Prot-Buzzer: R17.2, U5.5 (GP2)
SW_TGL_1: C2.1, J6.1, SW1.1 (A)
SW_TGL_2: C3.1, J6.2, SW2.1 (A)
VCC: C5.1, Q2.3 (S), R14.1, R20.2, SW4.2 (B), U6.3 (VI)
VIN: C1.1, C6.1, C7.1, J3.2, J8.1, Q2.2 (D), R4.1, R5.1, U1.2 (Vin), U2.2 (Vin)

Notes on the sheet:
DCDC-Converter | 5.0V_{General}
Voltage-OUT_{ESC}
Protection-Circuit
Toggle-Switch
Voltage-OUT_{Sub}
Capacitor
DCDC-Converter | 5.0V_{Line}
3-terminal regulator | 3.3V
Voltage-OUT_{Relay}
Voltage-IN
